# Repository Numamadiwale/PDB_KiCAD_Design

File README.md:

# PDB_KiCAD_Design
Contains all the files such as the schematic, PCB layout and Gerber files for power distribution board. there is a need for optimization in terms of space and wiring. Though a standard circuit for a generic PDB , This circuit was designed with a Quadcopter in mind. 

* The pins were added based on the ESP 32 models , the distance between the pin rows is 24.5 mm 
* 2 470 micro farad capacitors and 1 polarized capacitor to protect the components from a sudden spike in voltage.
* A voltage regulator to ensure 5 V is safely supplied to the board.
* 4 Connect pins for ESCs for the connection of BLDC motors.
* The folowing was designed with a 3S LiPo battery in mind.
* A male Xt60 Connector was used for the battery connection.

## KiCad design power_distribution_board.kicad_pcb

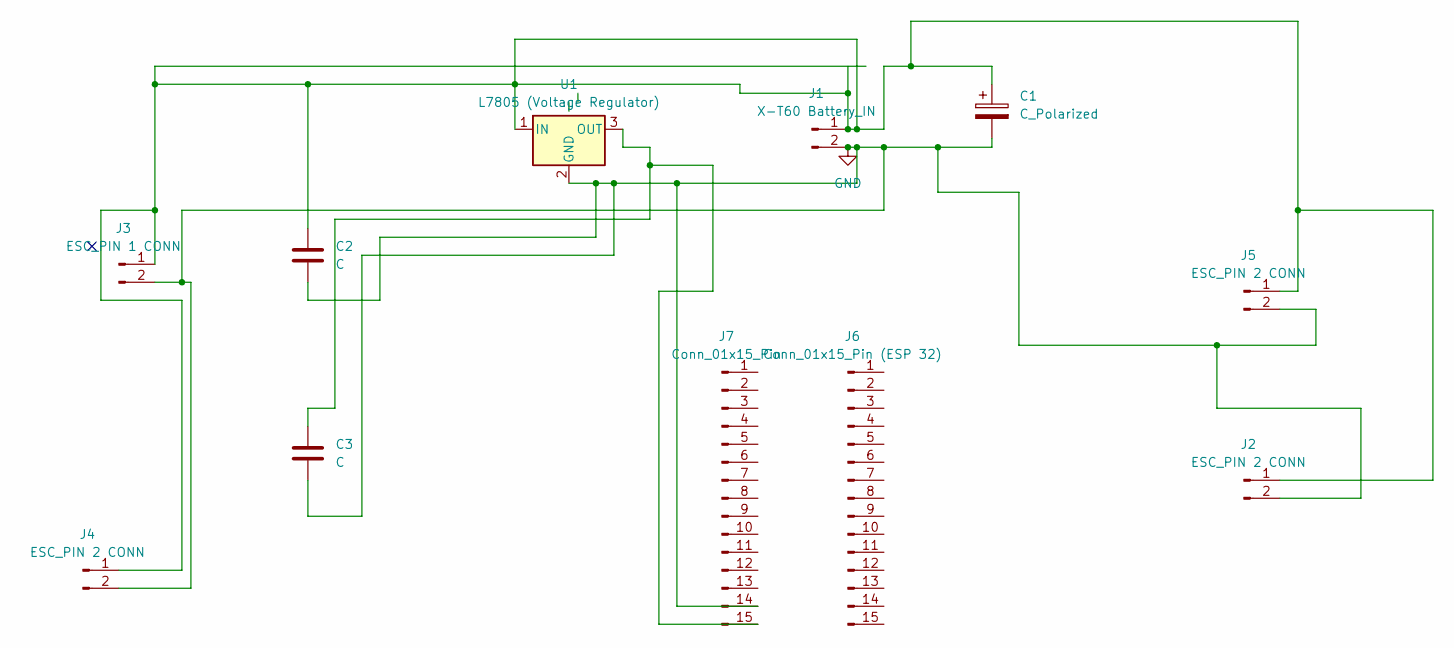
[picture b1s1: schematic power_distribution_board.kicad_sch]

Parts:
C1: C_Polarized; CP_Radial_D8.0mm_P3.50mm
C2, C3: C; CP_Radial_D8.0mm_P3.50mm
J1: X-T60 Battery_IN; AMASS_XT60-M_1x02_P7.20mm_Vertical
J2, J4, J5: ESC_PIN 2 CONN; TerminalBlock_Phoenix_PT-1,5-2-3.5-H_1x02_P3.50mm_Horizontal
J3: ESC_PIN 1 CONN; TerminalBlock_Phoenix_PT-1,5-2-3.5-H_1x02_P3.50mm_Horizontal
J6: Conn_01x15_Pin (ESP 32); PinHeader_1x15_P2.54mm_Vertical
J7: Conn_01x15_Pin; PinHeader_1x15_P2.54mm_Vertical
U1: L7805 (Voltage Regulator); TO-220-3_Vertical

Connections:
GND: C1.2, C2.2, C3.2, J1.2, J2.2, J3.2, J4.2, J5.2, J7.14 (GND), U1.2 (GND)
unnamed: C1.1, C2.1, J1.1, J2.1, J3.1, J4.1, J5.1, U1.1 (IN)
unnamed: C3.1, J7.15 (VIN), U1.3 (OUT)

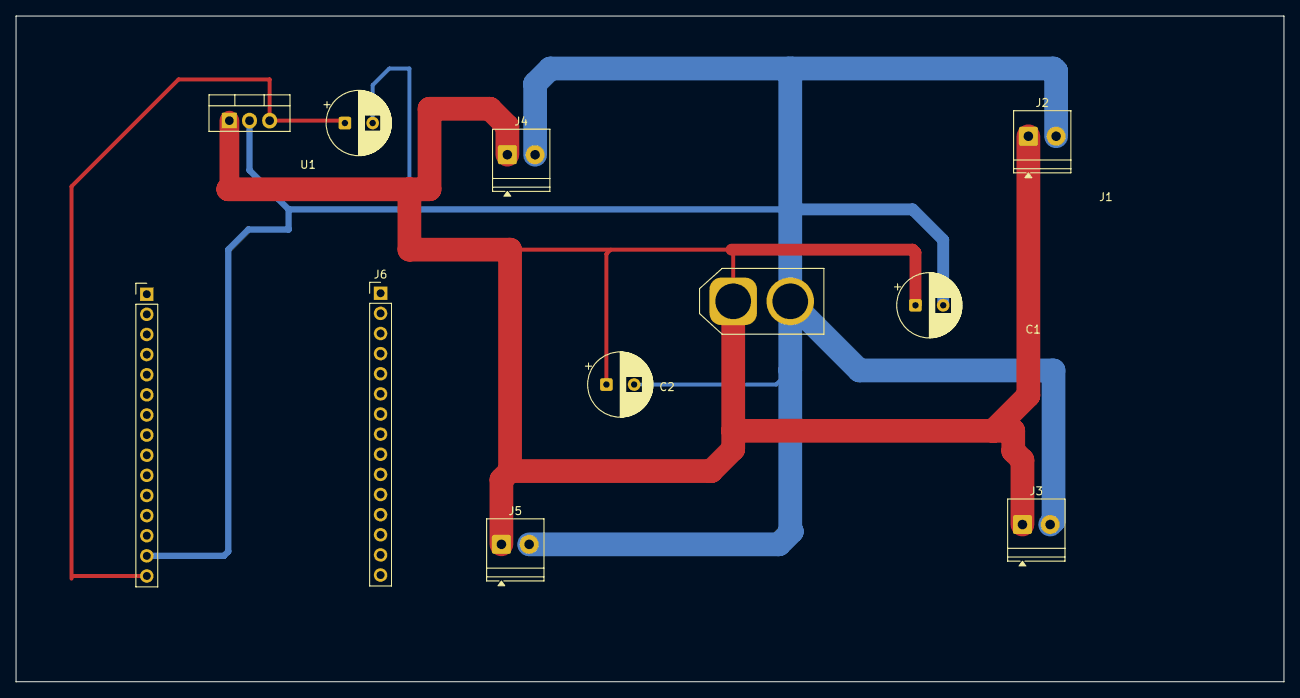
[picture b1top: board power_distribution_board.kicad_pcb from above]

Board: 2 copper layers, 160.0 x 84.0 mm, 11 parts (0 on the bottom side), 3 nets.

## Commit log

2026-02-19 Update README.md
    Added final PCB layout
2026-02-20 Add files via upload
    Added the Schematic layout, PCB layout and the GERBER files of the power distribution board.
